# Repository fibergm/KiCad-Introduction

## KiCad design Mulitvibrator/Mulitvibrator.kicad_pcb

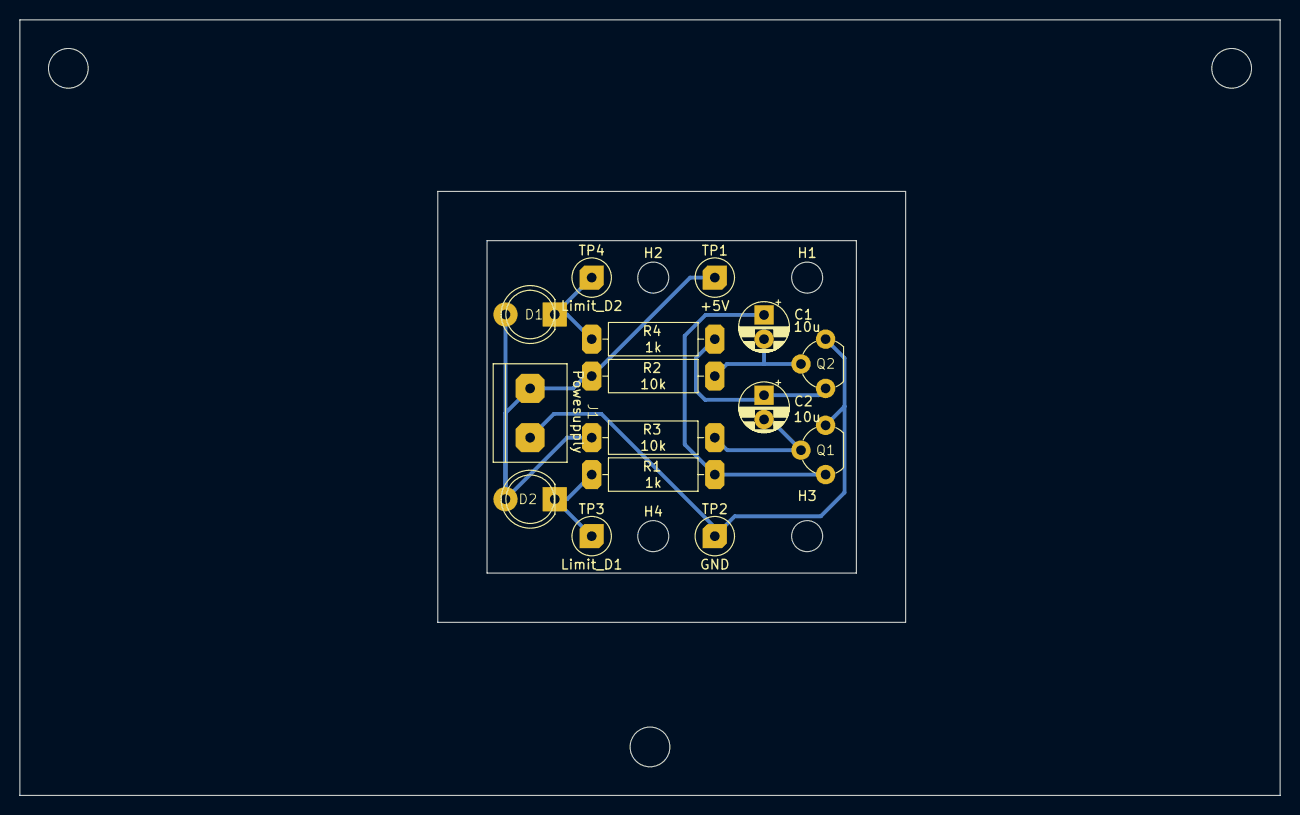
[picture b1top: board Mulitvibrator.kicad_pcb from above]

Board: 2 copper layers, 130.0 x 80.0 mm, 19 parts (0 on the bottom side), 8 nets.

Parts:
C1, C2: 10u; 1-10uF
D1, D2: D; LED 5mm
H1, H2, H3, H4: MountingHole; MountingHole_3.2mm_M3
J1: Powesupply; Terminal 2 Pol
Q1, Q2: BC546; TO-92
R1, R4: 1k; Resistor
R2, R3: 10k; Resistor
TP1: +5V; TestPoint
TP2: GND; TestPoint
TP3: Limit_D1; TestPoint
TP4: Limit_D2; TestPoint

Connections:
+5V: D1.2 (A), D2.2 (A), J1.1, R2.1, R3.1, TP1.1
/Base_Q1: C2.2, Q1.2 (B), R3.2
/Base_Q2: C1.2, Q2.2 (B), R2.2
/Limit_D1: D2.1 (K), R1.1, TP3.1
/Limit_D2: D1.1 (K), R4.1, TP4.1
/Pre_Q1: C1.1, Q1.1 (C), R1.2
/Pre_Q2: C2.1, Q2.1 (C), R4.2
GND: J1.2, Q1.3 (E), Q2.3 (E), TP2.1

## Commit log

2025-10-28 Overview Sheets V1
2025-10-31 Uploaded all the Libs and Spice Models
2025-10-31 Updated Links
2025-10-31 Added Example Project
2025-10-31 Updated a few Footprints
